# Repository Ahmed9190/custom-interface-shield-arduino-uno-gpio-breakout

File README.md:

# Custom Interface Shield — Arduino Uno GPIO Breakout

A two-layer shield that maps every Arduino Uno GPIO pin to labeled external 2.54 mm headers. Perfect for learning PCB design, DRC, and silkscreen discipline.

## Features

- Maps all Arduino Uno GPIO pins to labeled 2.54mm headers
- Digital pins D0–D13 breakout (D0–D7 and D8–D13 as separate headers)
- Analog pins A0–A5 breakout
- Power rail header (IOREF, RESET, 3V3, 5V, GND, GND, VIN)
- I2C sub-header (GND, VCC, SDA, SCL)
- UART sub-header (GND, VCC, TX, RX)
- SPI sub-header (2×3 pin header)
- Power LED indicator
- Reset button with debounce capacitor

## Pinout

### Arduino Stacking Headers (CN1–CN4)

| Header | Description |
|--------|-------------|
| CN1 | Power (7-pin): IOREF, RESET, +3V3, +5V, GND, GND, VIN |
| CN2 | Analog (6-pin): A0–A5, SDA/A4, SCL/A5 |
| CN3 | Digital Low (8-pin): D0–D7 |
| CN4 | Digital High (10-pin): D8–D13, GND, AREF, SDA/A4, SCL/A5 |

### Breakout Headers

| Ref | Description | Pins |
|-----|-------------|------|
| J3 | Digital Low | D0–D7 |
| J4 | Digital High | D8–D13, GND, AREF, SDA, SCL |
| J5 | Analog | A0–A5 |
| J6 | Power Rail | IOREF, RESET, 3V3, 5V, GND, GND, VIN |
| J7 | I2C | GND, 3V3, SDA, SCL |
| J8 | UART | GND, 5V, TX, RX |
| J9 | SPI | MISO, MOSI, SCK, SS, 5V, GND |

## Components

| Ref | Description | Footprint |
|-----|-------------|-----------|
| CN1–CN4 | Arduino Uno stacking headers | PinSocket 2.54mm |
| J3–J9 | Breakout headers | PinHeader 2.54mm |
| D1 | Green 3mm LED | LED_D3.0mm |
| R1 | 330Ω resistor | AXIAL_0.3 |
| C1 | 100nF capacitor (RESET debounce) | C_Disc_D5 |
| SW1 | Tactile reset button | SW_PUSH_6mm |

## PCB Specifications

- **Dimensions:** 68.6mm × 53.3mm (standard Uno shield size)
- **Layers:** 2-layer (Top: components + signals, Bottom: solid GND fill)
- **Thickness:** 1.6mm FR4
- **Finish:** HASL (Green solder mask)

## Design Notes

- C1 acts as a RESET debounce capacitor connected to SW1
- LED (D1) provides power-on indication
- CN4 includes SDA/A4 and SCL/A5 pins matching the actual Arduino Uno R3 pinout
- All THT components for easy hand-soldering

## License

MIT

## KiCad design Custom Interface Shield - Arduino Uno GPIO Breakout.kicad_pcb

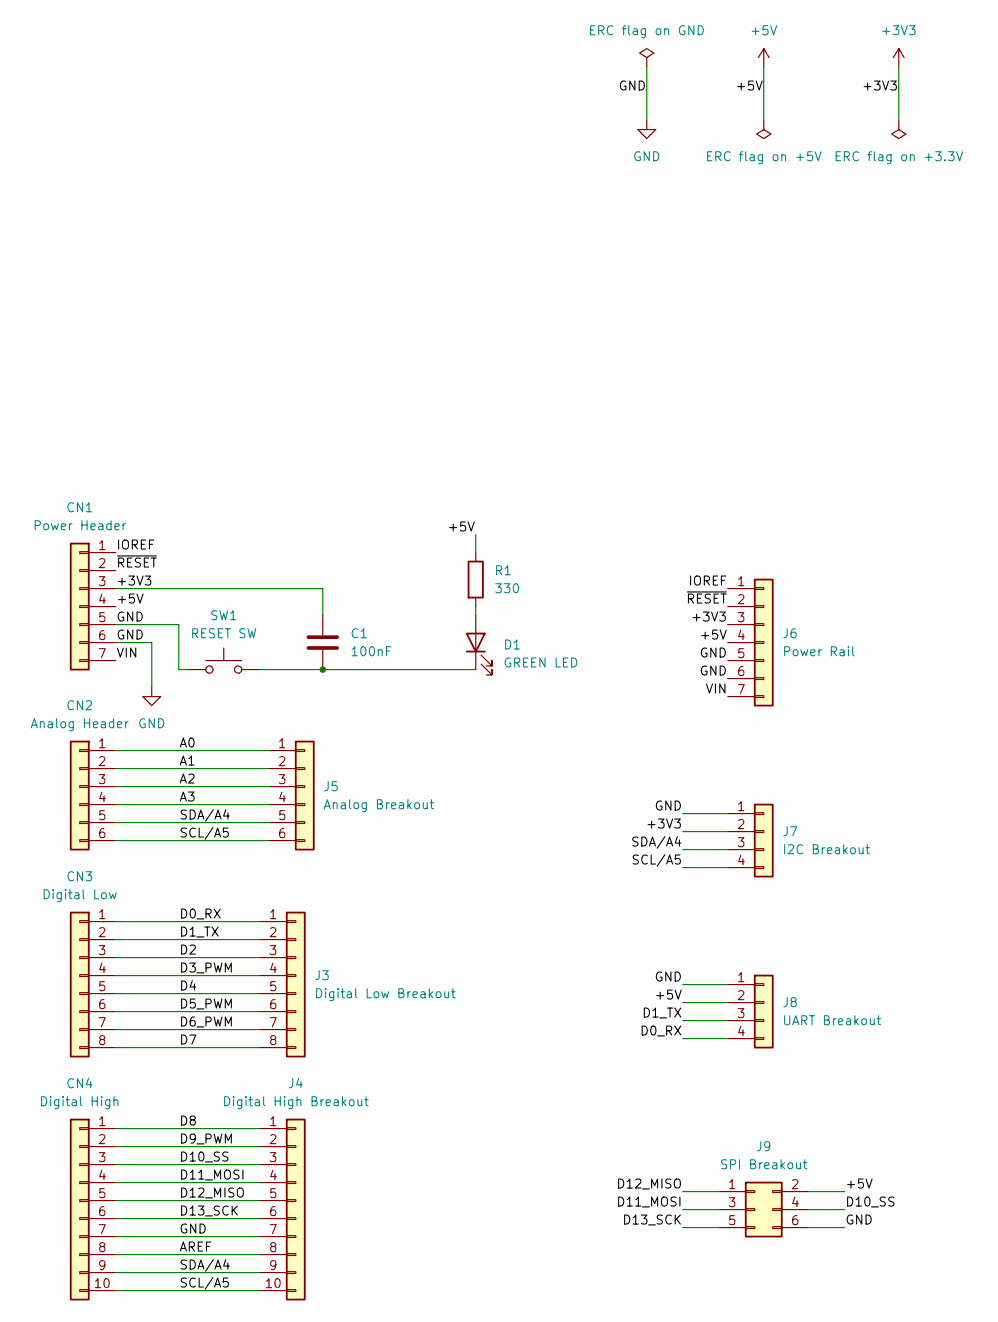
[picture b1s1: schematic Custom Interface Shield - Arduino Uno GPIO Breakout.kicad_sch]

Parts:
C1: 100nF; C_Disc_D5.0mm_W2.5mm_P2.50mm
CN1: Power Header; PinSocket_1x07_P2.54mm_Vertical
CN2: Analog Header; PinSocket_1x06_P2.54mm_Vertical
CN3: Digital Low; PinSocket_1x08_P2.54mm_Vertical
CN4: Digital High; PinSocket_1x10_P2.54mm_Vertical
D1: GREEN LED; LED_D3.0mm
J3: Digital Low Breakout; PinHeader_1x08_P2.54mm_Vertical
J4: Digital High Breakout; PinHeader_1x10_P2.54mm_Vertical
J5: Analog Breakout; PinHeader_1x06_P2.54mm_Vertical
J6: Power Rail; PinHeader_1x07_P2.54mm_Vertical
J7: I2C Breakout; PinHeader_1x04_P2.54mm_Vertical
J8: UART Breakout; PinHeader_1x04_P2.54mm_Vertical
J9: SPI Breakout; PinHeader_2x03_P2.54mm_Vertical
R1: 330; R_Axial_DIN0204_L3.6mm_D1.6mm_P7.62mm_Horizontal
SW1: RESET SW; SW_PUSH_6mm

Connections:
+3V3: C1.1, CN1.3, J6.3, J7.2
+5V: CN1.4, J6.4, J8.2, J9.2, R1.1
/A0: CN2.1, J5.1
/A1: CN2.2, J5.2
/A2: CN2.3, J5.3
/A3: CN2.4, J5.4
/AREF: CN4.8, J4.8
/D0_RX: CN3.1, J3.1, J8.4
/D1_TX: CN3.2, J3.2, J8.3
/D2: CN3.3, J3.3
/D3_PWM: CN3.4, J3.4
/D4: CN3.5, J3.5
/D5_PWM: CN3.6, J3.6
/D6_PWM: CN3.7, J3.7
/D7: CN3.8, J3.8
/D8: CN4.1, J4.1
/D9_PWM: CN4.2, J4.2
/D10_SS: CN4.3, J4.3, J9.4
/D11_MOSI: CN4.4, J4.4, J9.3
/D12_MISO: CN4.5, J4.5, J9.1
/D13_SCK: CN4.6, J4.6, J9.5
/IOREF: CN1.1, J6.1
/SCL/A5: CN2.6, CN4.10, J4.10, J5.6, J7.4
/SDA/A4: CN2.5, CN4.9, J4.9, J5.5, J7.3
/VIN: CN1.7, J6.7
/~RESET: CN1.2, J6.2
GND: CN1.5, CN1.6, CN4.7, J4.7, J6.5, J6.6, J7.1, J8.1, J9.6, SW1.1
unnamed: D1.2 (A), R1.2
unnamed: C1.2, D1.1 (K), SW1.2

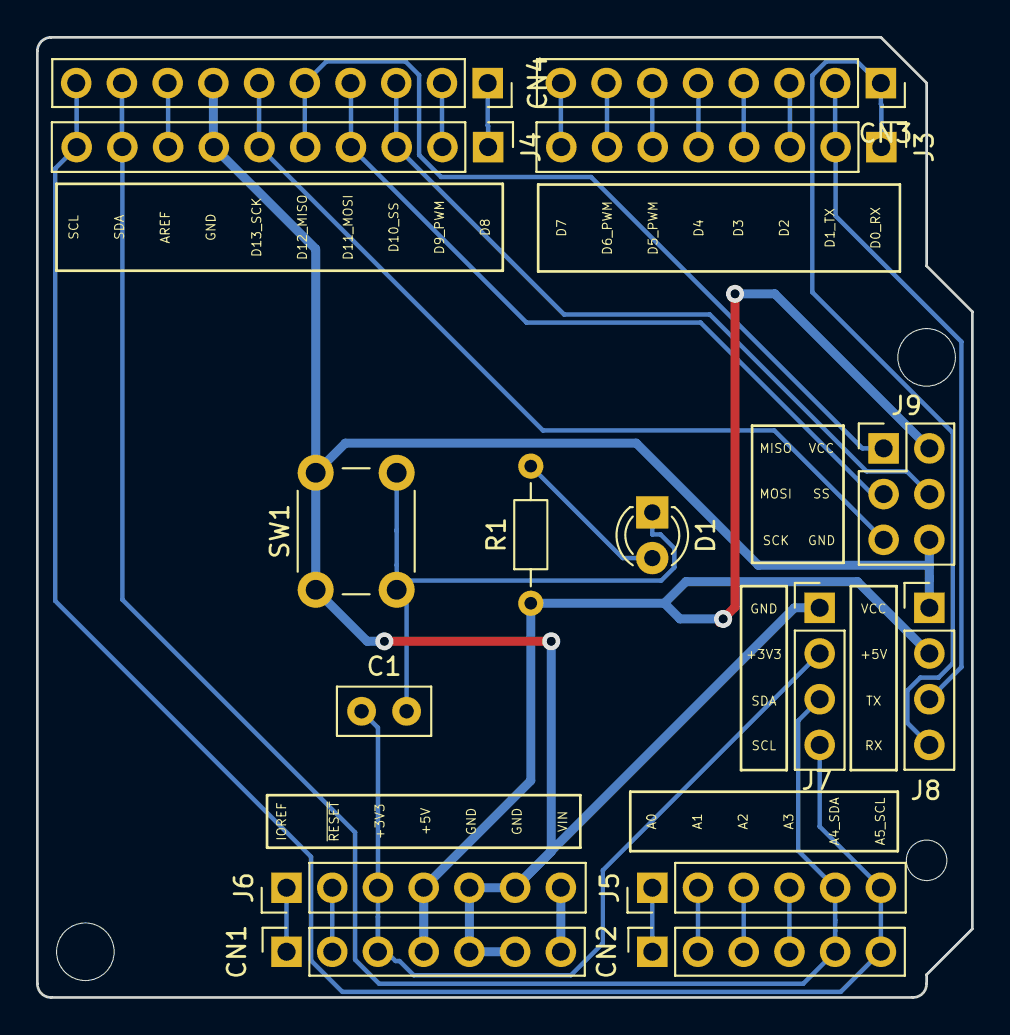
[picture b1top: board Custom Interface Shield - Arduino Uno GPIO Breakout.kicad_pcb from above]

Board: 2 copper layers, 51.9 x 53.3 mm, 18 parts (0 on the bottom side), 29 nets.

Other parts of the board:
MH2, MH3, MH4: MountingHole_3.2mm

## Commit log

2026-03-01 Initial commit with README and photos
2026-03-01 Update README with concise documentation and photos
2026-03-01 Add KiCad .gitignore
2026-03-01 Update README with accurate pinout and schematic
2026-03-01 Add all KiCad project files
